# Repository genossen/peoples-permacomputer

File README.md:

# The People's Permacomputer Project

The People's Permacomputer (henceforth known as "the people's
computer", or "the permacomputer") is a project dedicated to
resourcing the specification, and then construction of a
'permacomputer'.

1. [Who are the people running this project?](https://sr.ht/~vidak/peoples-permacomputer/#who)
2. [What is a permacomputer?](https://sr.ht/~vidak/peoples-permacomputer/#what-is-a-permacomputer)
3. [What is the point of this project?](https://sr.ht/~vidak/peoples-permacomputer/#what-is-the-point-of-this-project)
4. [What distinguishes this project from the others?](https://sr.ht/~vidak/peoples-permacomputer/#mutual-exclusion)
5. [What previous historical traditions inspire this project?](https://sr.ht/~vidak/peoples-permacomputer/#adventures-in-the-traditions-of-computation)

## Who?

*"The Committee"*

- [50hz](https://cathode.church/@50htz)

- [vidak](https://anticapitalist.party/@dirtycommo)
 
- [project social media profile](https://retro.social/@permacomputer) 

- [BASIC forum](https://basiclang.solarpunk.au/)

- [Solarpunk BASIC Archive](https://archive.basiclang.solarpunk.au)
 
_Yes you can join the committee_.

## What is a permacomputer?

### TL/DR

The ultimate goal of the project is to construct computers which will
last a _really_ long time, and still stay operational.

### Are you serious?

This project should largely be regarded as a piece of art. If someone
finds some practical use for what we are building, however, that would
also give us joy.

### Is this a kit project?

It is a project pipe-dream to end up manufacturing permacomputer units
at a kind of cottage-industry level, perhaps something for a worker's
co-operative to do. These units will be really, really cheap--if it's
not cheap, it's not accessible to the poor.

## What is the point of this project?

The original purpose of this project was to design and then construct
computers that would be able to survive a societal collapse.

After working on the project, it became apparent that the point of the
project should not be to imagine a hypothetical future, but to engage
practically with the problems of the present.

The entire computing stack of the modern era is large, confusing, and
unsafe. People would rather excuse themselves from having to learn
about it. Who can blame them?

The first aim of the project is to be exceedingly cost effective: "if
the oppressed cannot access some technology, then it is not
revolutionary".

The second aim of the project is the promotion of digital
literacy. Digital literacy should promote a joyful user experience
that is non-exploitative. It should also foster a sense of
community--"no-one is an island".

To this end, the scope of the people's permacomputer project was
deliberately limited to programs around or just over 100
lines. Definitely not more than 200.

The project therefore decided to investigate BASIC as the paradigmatic
human-computer interface for the permacomputer.

For the application towards which it was targeted, the investigation
the project has done so far into BASIC has been fruitful, and even
quite surprising--the 70s/80s hobby computing scene was far richer and
more creative than the project previously assumed: not less than five
(5) different text editors in BASIC were unearthed!

[OLD](about/project-purpose.md).

## Mutual exclusion

There are many influential projects which attempt to address the same
set of values driving the people's permacomputer project. Some worthy
of note can be listed in no particular order:

- [Collapse OS](http://collapseos.org/).
- [uxn](https://100r.co/site/uxn.html).
- The [RC2014](https://rc2014.co.uk/) computer kit.
- Ben Eater's [6502 project](https://eater.net/6502) video series.

All of these projects are concerned with some subset of the principles
the permacomputer project holds dear. Collapse OS is software that
aims to be system agnostic, and assumes the previous acquisition of
some supported hardware.

[READ MORE](about/mutual-exclusion.md)

## Adventures in the traditions of computation

We seem to take it for granted that a computer in everyone's hand just
is democratic computing. Indeed, the ubiquity of contemporary
computation has been confused for 'democracy'.

As quickly as we marched towards computing for the masses, we marched
just as swiftly away.

[OUR INSPIRATION](about/inspiration.md)

[PROJECT RESULTS](results/results-index.md)

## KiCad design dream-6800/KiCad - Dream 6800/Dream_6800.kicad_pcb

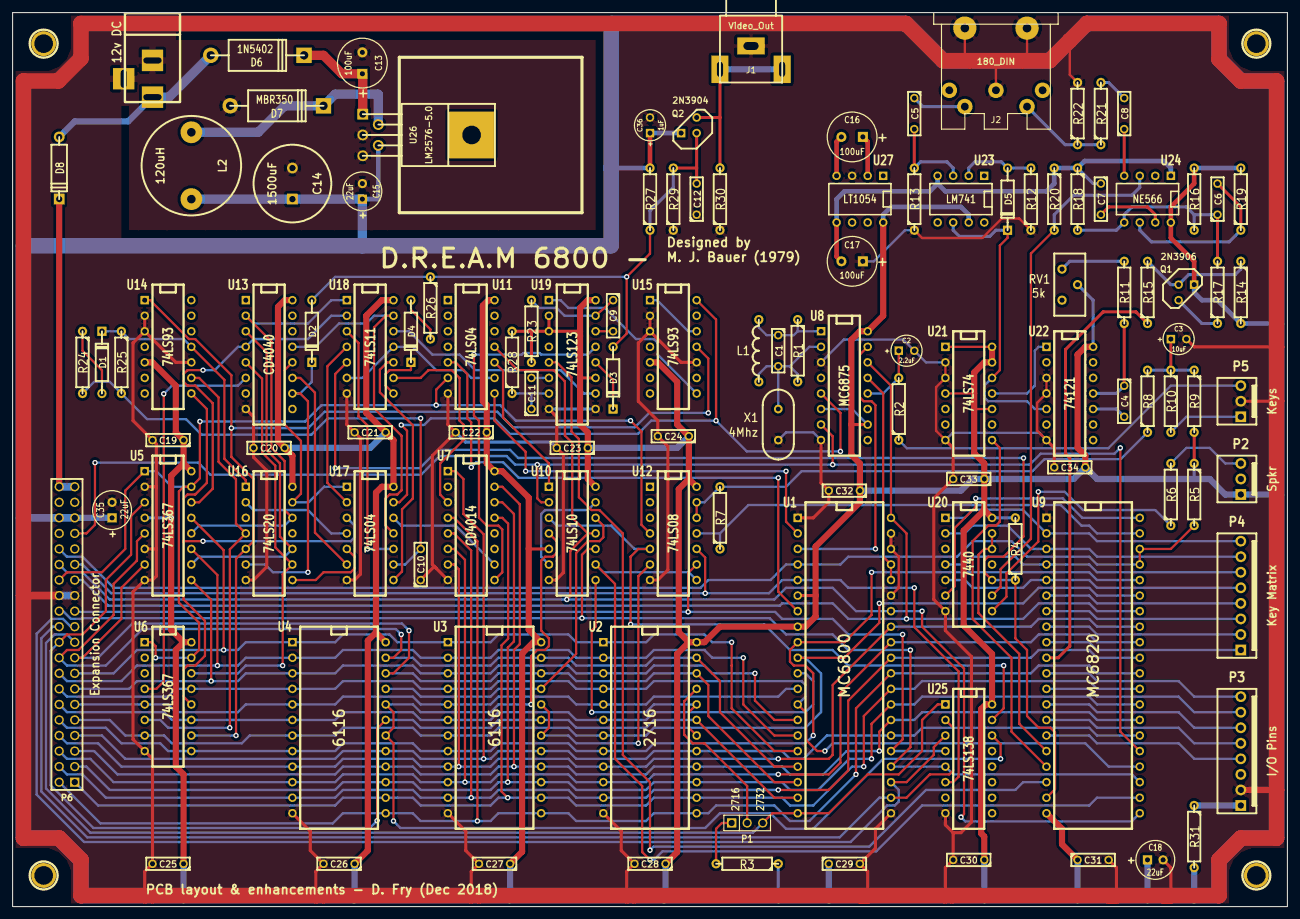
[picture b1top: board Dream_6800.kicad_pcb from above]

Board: 2 copper layers, 208.3 x 146.1 mm, 121 parts (0 on the bottom side), 137 nets.

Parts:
12v DC: 12v DC; BARREL_JACK
C1, C9: 150pF; C2
C2: 2.2uF; C1V5
C3: 10uF; C1V5
C4: 33nF; C2
C5, C8: 10nF; C2
C6: 1nF; C2
C7: 22nF; C2
C10: 3n3; C2
C11, C19, C20, C21, C22, C23, C24, C25, C26, C27, C28, C29, C30, C31, C32, C33, C34: 100nF; C2
C12: 47pf; C2
C13, C16, C17: 100uF; C1V8
C14: 1500uF; C2V12
C15, C18, C35: 22uF; C1V7
C36: 1uF; C1V5
D1, D2, D3, D4: 1N4148; DO-41
D5: BAT43; DO-41
D6: 1N5402; MBR350
D7: MBR350
D8: 1N4002; D4
J1: Video_Out; PhonoSkt
J2: 180_DIN; 180 DIN 5p
L1: 10uH; Choke_Ax_01
L2: 120uH; Choke_07
P1: EPROM; PIN_ARRAY_3X1
P2: Spkr; VinKK3
P3: I/O Pins; VinKK8
P4: Key Matrix; VinKK8
P5: Keys; VinKK3
P6: Expansion Connector; PIN_ARRAY_20X2
P7, P8, P9, P10: CONN_1; 1pin
Q1: 2N3906; TO92
Q2: 2N3904; TO92
R1: 1k; R4
R2: 100R; R4
R3, R7, R20: 4k7; R4
R4, R5, R9, R22, R27, R29: 2k2; R4
R6: 47; R4
R8, R26: 470; R4
R10, R25: 220; R4
R11, R14, R18, R23, R28: 10k; R4
R12, R13: 22k; R4
R15, R16, R17: 1k5; R4
R19: 5k6; R4
R21: 6k8; R4
R24: 120; R4
R30: 75; R4
R31: 10; R4
RV1: 5k; RV_Bourns3386H
U1: MC6800; DIP-40__600
U2: 2716; DIP-24__600
U3, U4: 6116; DIP-24__600
U5, U6: 74LS367; DIP-16__300
U7: CD4014; DIP-16__300
U8: MC6875; DIP-16__300
U9: MC6820; DIP-40__600
U10: 74LS10; DIP-14__300
U11, U17: 74LS04; DIP-14__300
U12: 74LS08; DIP-14__300
U13: CD4040; DIP-16__300
U14, U15: 74LS93; DIP-14__300
U16: 74LS20; DIP-14__300
U18: 74LS11; DIP-14__300
U19: 74LS123; DIP-16__300
U20: 7440; DIP-14__300
U21: 74LS74; DIP-14__300
U22: 74121; DIP-14__300
U23: LM741; DIP-8__300
U24: NE566; DIP-8__300
U25: 74LS138; DIP-16__300
U26: LM2576-5.0; TO220-5H
U27: LT1054; DIP-8__300
X1: 4Mhz; HC-49V

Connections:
02: P6.33, U8.7, U9.25, U10.2
2FO: U8.5, U15.14, U17.13
+5v: C14.1, C15.1, C18.1, C19.1, C20.1, C21.1, C22.1, C23.1, C24.1, C25.1, C26.1, C27.1, C28.1, C29.1, C30.1, C31.1, C32.1, C33.1, C34.1, C35.1, C36.1, L2.2, P2.1, P6.35, P6.36, Q1.1, Q2.1, R3.1, R4.2, R5.1, R9.2, R14.2, R16.2, R19.2, R23.1, R27.2, R28.2, R31.2, RV1.2, U1.6, U1.8, U2.24, U3.24, U4.24, U5.4, U5.16, U6.16, U7.16, U8.6, U8.10, U8.16, U9.20, U10.5, U10.14, U11.14, U12.14, U13.16, U14.5, U15.5, U16.14, U17.14, U18.14, U19.2, U19.3, U19.11, U19.16, U20.14, U21.1, U21.4, U21.10, U21.13, U21.14, U22.14, U23.7, U24.8, U25.16, U26.4, U27.8
+12v: D8.2, P6.39, P6.40
-5V: C7.1, C17.2, R18.1, R20.1, U23.4, U24.1, U27.5
/Keyboard/PB1: P3.8, U9.11
/Keyboard/PB2: P3.7, U9.12
/Keyboard/PB3: P3.6, U9.13
/Keyboard/PB4: P3.5, U9.14
/Keyboard/PB5: P3.4, U9.15
/Memory/RAMCS0*: U3.18, U3.20, U12.6
/Memory/RAMCS1*: U4.18, U4.20, U10.4, U25.14
/Memory/RAMWR*: U3.21, U4.21, U10.12
/Memory/ROMCS*: U2.18, U2.20, U10.8
/Video/H1: U15.1, U15.12
/Video/H4: U15.8, U19.1
/Video/H8: U6.10, U14.1, U15.11, U16.5
/Video/H16: U6.6, U14.9, U16.4
/Video/H32: U6.12, U14.8, U17.3
/Video/H64: D1.2, R25.1, U14.11, U16.1
/Video/V1: U6.4, U13.6
/Video/V2: U6.14, U13.5, U16.9
/Video/V4: U5.10, U13.3, U16.10
/Video/V8: U5.12, U13.2, U16.12, U18.1
/Video/V16: U5.14, U13.4, U18.2
/Video/V32: U13.13, U17.11, U18.13
/Video/V64: U13.12, U16.13, U17.1
/Video/VERT-EN: U11.9, U18.6, U18.11
/Video/VSYNC*: D3.2, U19.12
A0: P6.10, U1.9, U2.8, U3.8, U4.8, U6.9, U9.36
A1: P6.9, U1.10, U2.7, U3.7, U4.7, U6.7, U9.35
A2: P6.12, U1.11, U2.6, U3.6, U4.6, U6.11
A3: P6.11, U1.12, U2.5, U3.5, U4.5, U6.5
A4: P6.14, U1.13, U2.4, U3.4, U4.4, U6.13, U9.24
A5: P6.13, U1.14, U2.3, U3.3, U4.3, U5.9
A6: P6.16, U1.15, U2.2, U3.2, U4.2, U5.11
A7: P6.15, U1.16, U2.1, U3.1, U4.1, U5.13
A8: P6.18, U1.17, U2.23, U3.23, U4.23, U5.5
A9: P6.17, U1.18, U2.22, U3.22, U4.22, U5.7
A10: P6.20, U1.19, U2.19, U3.19, U4.19, U5.3
A11: P1.3, P6.19, U1.20, U25.1
A12: P6.22, U1.22, U25.2
A13: P6.21, U1.23, U25.3
A14: P6.24, U1.24, U9.23, U10.10, U25.5
A15: P6.23, U1.25, U12.9, U25.4
BA: U1.7, U11.5
BA*: P6.28, U5.1, U5.15, U6.1, U6.15, U11.6, U12.4
CASS.IN: U9.17, U21.8
CASS.OUT: R15.1, U9.10
D0: P6.8, U1.33, U2.9, U3.9, U4.9, U7.7, U9.33
D1: P6.6, U1.32, U2.10, U3.10, U4.10, U7.6, U9.32
D2: P6.4, U1.31, U2.11, U3.11, U4.11, U7.5, U9.31
D3: P6.2, U1.30, U2.13, U3.13, U4.13, U7.4, U9.30
D4: P6.1, U1.29, U2.14, U3.14, U4.14, U7.13, U9.29
D5: P6.3, U1.28, U2.15, U3.15, U4.15, U7.14, U9.28
D6: P6.5, U1.27, U2.16, U3.16, U4.16, U7.15, U9.27
D7: P6.7, U1.26, U2.17, U3.17, U4.17, U7.1, U9.26
DMA.ENAB: R4.1, U9.19, U18.5, U20.10
EXT-RST: P5.3, R2.1
GND: 12v DC.2, 12v DC.3, C2.2, C3.2, C10.1, C12.1, C13.2, C14.2, C15.2, C17.1, C18.2, C19.2, C20.2, C21.2, C22.2, C23.2, C24.2, C25.2, C26.2, C27.2, C28.2, C29.2, C30.2, C31.2, C32.2, C33.2, C34.2, C35.2, C36.2, D7.1, J1.3, J2.2, J2.6, J2.7, P3.2, P5.2, P6.25, P6.26, R12.1, R13.1, R22.2, R29.1, R30.1, U1.1, U1.21, U1.35, U1.38, U1.39, U2.12, U3.12, U4.12, U5.2, U5.6, U5.8, U6.8, U7.8, U8.3, U8.8, U9.1, U10.7, U11.7, U12.7, U13.8, U14.2, U14.3, U14.10, U15.2, U15.3, U15.10, U16.7, U17.7, U18.7, U19.8, U19.9, U20.7, U21.2, U21.3, U21.7, U22.3, U22.4, U22.7, U25.8, U26.3, U26.5, U27.3, X1.1
HALT*: U1.2, U11.8
IRQ*: P6.32, R5.2, U1.4, U9.37, U9.38
unnamed: C1.2, L1.1, R1.2, U8.2, X1.2
unnamed: C1.1, L1.2, R1.1, U8.1
unnamed: U1.3, U8.15
unnamed: U1.36, U1.37, U8.13
unnamed: C2.1, R2.2, U8.12
unnamed: U10.6, U10.13
unnamed: U10.1, U11.10
unnamed: U10.3, U12.5, U25.15
unnamed: P1.2, U2.21
unnamed: P1.1, R3.2
unnamed: P5.1, R10.2
unnamed: P4.4, U9.6
unnamed: P4.2, U9.8
unnamed: U9.40, U20.6
unnamed: R7.1, U9.39, U12.11
unnamed: P4.3, U9.7
unnamed: P4.6, U9.4, U20.4
unnamed: P4.8, U9.2, U20.1
unnamed: P4.1, U9.9
unnamed: P3.1, R31.1
unnamed: P2.3, R6.2
unnamed: P4.5, U9.5, U20.5
unnamed: P4.7, U9.3, U20.2
unnamed: R6.1, U20.8
unnamed: R7.2, R8.1, U12.12, U12.13
unnamed: C3.1, R8.2, R9.1, R10.1
unnamed: U9.16, U20.12, U20.13
unnamed: R11.2, RV1.1
unnamed: J2.5, R21.1, R22.1
unnamed: Q1.3, R17.1
unnamed: C8.1, U24.4
unnamed: C7.2, U24.7
unnamed: C6.2, R19.1, U24.6
unnamed: C6.1, R16.1, R17.2, R18.2, U24.5
unnamed: Q1.2, R14.1, R15.2
unnamed: C8.2, R21.2
unnamed: C5.1, J2.4
unnamed: C5.2, R13.2, U23.3
unnamed: C4.2, U22.10
unnamed: C4.1, R11.1, U22.11
unnamed: U21.11, U22.1
unnamed: D5.2, U21.12, U22.5, U23.6
unnamed: D5.1, R12.2, U23.2
unnamed: D2.2, U13.10, U16.6
unnamed: C11.2, U19.6
unnamed: U18.12, U19.10
unnamed: C12.2, D2.1, D3.1, Q2.2, R26.1, R27.1, R29.2
unnamed: U13.11, U17.6
unnamed: U16.8, U17.5
unnamed: D1.1, R24.1
unnamed: U17.10, U18.3
unnamed: U17.2, U18.4
unnamed: C11.1, R28.1, U19.7
unnamed: J1.1, J1.2, Q2.3, R30.2
unnamed: U16.2, U17.4
unnamed: C9.2, U19.14
unnamed: C9.1, R23.2, U19.15
unnamed: U7.9, U19.13
unnamed: D4.1, R26.2
unnamed: D4.2, U18.8
unnamed: U7.10, U17.12
unnamed: U17.8, U18.10
unnamed: C10.2, R24.2, R25.2, U17.9
unnamed: U7.3, U18.9
unnamed: D7.2, L2.1, U26.2
unnamed: 12v DC.1, D6.1, D8.1
unnamed: C13.1, D6.2, U26.1
unnamed: C16.1, U27.2
unnamed: C16.2, U27.4
R/W*: P6.30, U1.34, U9.21, U10.11, U11.11
RST*: P6.27, U1.40, U8.14, U9.34
RTC: U9.18, U19.5
VCO: R20.2, U20.9, U24.3
VMA: P6.29, U1.5, U12.10, U25.6
VMA.A15: U9.22, U10.9, U12.8

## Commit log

2024-02-21 initial commit, README.md created
2024-02-21 copying over previous research
2024-02-21 adding more chip-8 documentation
2024-02-23 adding more PDFs
2024-02-23 README tinkering
2024-02-23 README writing
2024-02-27 cleaning up
2024-02-27 more work on the README
2024-02-27 still writing the README
2024-02-27 README
2024-03-07 parts sourcing list
2024-07-27 phase two documentation begin
2024-07-27 filling out phase two README
2024-07-27 testing out including fedi quotations
2024-07-27 finishing up on phase 1 results section
2024-07-27 fixes
2024-07-27 more fixes
2024-07-27 draft 1 done
2024-07-27 draft 1 fixes 1
2024-07-27 draft 1 fixes 2
2024-11-28 begin phase two~
2024-11-28 begin phase two - cleanup
2024-11-28 begin phase two - cleanup 2
2024-11-28 public domain licence
2024-11-28 cleanup
2024-11-28 fixing fedi accounts
2024-12-05 reorganising...
2024-12-05 damn these backup files
2024-12-05 learning how all this wiki stuff works
2024-12-05 added logo and social media profile link
2024-12-05 need to add the image...
2024-12-05 try HTML?
2024-12-05 magical URLs
2024-12-05 adding logs
2024-12-05 adding log link
2024-12-05 adding more logs
2024-12-05 i am some sort of fool
2024-12-05 yep, confirmed
2025-06-22 project refresh june 2025
    modified: ../README.md
    2025-06-22-project-refresh.md
2025-06-22 add new log file
2025-06-22 removing autosave file
2025-06-26 added images
2025-06-26 added type-in text editor listings
2025-06-26 colour correction on led listing
2025-06-26 fixups
2025-06-26 begun transcription of LED.BAS
2025-06-26 removing autosave
2025-06-26 phase 2 results write up
2025-06-26 fixing image embed
2025-06-26 more edits to phase 2 results
2025-06-26 more about the actual MCU VDP chosen
2025-06-26 republishing the grant searle MCU video processor as a summary
2025-06-26 continuing to edit
2025-06-26 continuing to edit #2
2025-06-26 continuing to edit #3
2025-06-26 add image
2025-06-26 draft #2
2025-06-26 README update june 2025
2025-06-26 old readme
2025-06-26 added phase 2 toc
2025-06-27 continuing to transcribe led.bas
2025-06-27 transcription of led.bas finished
2025-06-27 added two BASIC game listings
2025-06-27 added BBC BASIC users guide
2025-06-27 led.bas README transcribed
2025-06-27 simplifying and updating main README
2025-06-27 still simplifying
2025-06-27 still simplifying, last section, inspiration.
2025-06-27 preparing to add phase 3
2025-06-27 preparing to add phase 3 - #2
2025-06-27 adding phase-3.md
2025-06-27 deleting autosave file
2025-06-27 fixing links
2025-06-27 adding type in BASIC text editors
2025-06-27 fixing formatting
2025-06-27 adding VIC EDITYPE
2025-06-27 fixing link
2025-06-27 adding links, filling out
2025-06-27 more filling out
2025-06-27 final edit to main README
2025-06-28 added wrdpro.bas
2025-06-28 updating phase-3.md
2025-06-28 adding to phase-3.md
2025-06-28 added wrdpro README
2025-06-28 adding links
2025-06-28 more updates
2025-06-28 added vicstation images
2025-06-28 image size fix
2025-06-28 giving up... :(
2025-06-28 filling out phase-3.md
2025-06-28 added vicstation - file reader images
2025-06-28 testing anchors
2025-06-28 7 programs now listed
2025-06-28 about one third through wrdpro.bas transcription
2025-06-28 about half way through wrdpro.bas transcription
2025-06-28 adding utility.bas folder
2025-06-28 remove autosave file
2025-06-28 two pages left
2025-06-28 tinybasic submodule
2025-06-28 wrdpro.bas transcription draft 1 complete
2025-06-28 phase-3.md update
2025-06-28 cleaning up images
2025-06-28 formatting phase-3.md
2025-06-28 more formatting phase-3.md
2025-06-29 conversions pending
2025-06-29 copied over documentation from tinybasic MANUAL.md
2025-06-29 added conversions research to main README
2025-06-29 EDITYPE.BAS currently @ 4.8KB... maybe we can fit it all into resident memory?
2025-06-30 EDITYPE.BAS transcription finished. 5.4K. will fit in memory .
2025-07-02 three altair (8K) BASIC text editors added from Computer Notes 1977 October
2025-07-03 begun EDIT.BAS transcription
2025-07-03 adding some files that need to be tracked
2025-07-05 added correspondence from Stefan's BASIC dev
2025-07-06 lots of ASCII art...
2025-07-06 filling out more about EDIT.BAS
2025-07-06 started EDIT.BAS README
2025-07-06 filling out more of the EDIT.BAS README
2025-07-06 quite a difficult ASCII art table...
2025-07-18 working on edit.bas again
2025-07-18 edit.bas transcription complete
2025-07-18 continuing work on the edit.bas README
2025-07-18 edit.bas README table #2 complete
2025-07-18 edit.bas README final heading
2025-07-18 edit.bas README completed
2025-07-18 finishing up for edit.bas
2025-07-18 edit.bas bug fixes
2025-07-19 cleaning up and restructuring the repo
2025-07-19 clean up and slight restructure
2025-07-19 woopsie
2025-07-19 adding in phase-2 information
2025-07-19 the project will definitely have a focus phase on lisp, so these will be included
2025-07-19 the jupiter ace is just lovely, i could not not include it. also the assembly source to CPM. there is something interesting there, but i have yet to work out what it is...
2025-07-26 cleaning up a little
2025-07-26 continuing debugging of EDIT.BAS
2025-08-15 adding work not yet tracked
2025-08-15 fixing up overlong lines
2025-08-15 added comments about key program variables
2025-08-15 a bit of success!
2025-08-27 beginning skeleton of the code to port EDIT.BAS to Stefan's Tiny BASIC
2025-08-27 added tutorial file from Tiny BASIC repo
2025-08-27 that honestly may be enough to get it working...
2025-08-27 applying fixes from the noodling in the -port-draft-1 file
2025-08-27 update README somewhat
2025-08-28 beginning transcription of Atari BASIC SCRIPTOR.BAS
2025-08-28 updating README
2025-08-28 phase three results updated
2025-08-28 phase three results, include EDIT.BAS
2025-08-28 hyperlink fixes...
2025-08-28 typos
2025-08-28 hyperlink fixes... #2
2025-08-28 testing this...
2025-08-28 forgot my own structure
2025-08-28 hyperlink fixes... #3
2025-08-29 continuing transcription of SCRIPTOR.BAS
2025-08-29 continuing transcription of SCRIPTOR.BAS #2
2025-09-16 phase 4 recap begin
2025-09-16 link fix
2025-09-16 formatting fix
2025-09-16 filling out more
2025-09-16 tables
2025-09-25 redesigning the README
2025-09-25 simplifying the language
2025-09-25 results index page update
2025-09-25 fix link
2025-10-01 transcription work done for SCRIPTOR.BAS
2025-10-02 more transcription work on SCRIPTOR.BAS
2025-10-02 yet more transcription work on SCRIPTOR.BAS
2025-10-06 EDIT.BAS begins to start working...
2025-10-06 added log video
2025-10-09 SCRIPTOR.BAS transcription complete
2025-12-04 string arrays!
2025-12-04 string arrays are only supported in the Apple 1 flavour of this Tiny BASIC
2025-12-04 continuing to do compatibility fixes...
2025-12-04 beginning the process of the Lisp implementation of BASIC
2025-12-04 finishing up for tonight
2025-12-05 continuing with ECMA-55
2025-12-06 adding new links
2025-12-09 ECMA-55 constants chapter finished
2025-12-11 updated README includes new BASIC archive
2025-12-30 starting the process of finalising the EDIT text editor
2026-01-27 people's editor version 1.0
2026-01-27 hardcoded buffer limit :(
2026-01-27 fixing comment...
2026-04-25 started working on second version of people's text editor
2026-04-25 added sketch drawing program
2026-04-25 string arrays can be treated as pseudo-2D arrays, perhaps?
2026-04-25 got the main idea hammered out. onto GET, next...
2026-04-26 finished SKETCH transcription
2026-04-26 working on port to arduino now
2026-04-26 finished the guts of the sketch mode porting
2026-04-26 first draft of port finished.
2026-04-26 bug fix. finished. seems to be working.
2026-04-27 added BASIC turtle graphics translator, PILOT
2026-04-27 flight simulator added
2026-04-27 ignore backup files
2026-04-30 editype conversion begin
2026-04-30 first pass finished
2026-04-30 first port finished. adapted hard copy printer routines to display to the screen.
